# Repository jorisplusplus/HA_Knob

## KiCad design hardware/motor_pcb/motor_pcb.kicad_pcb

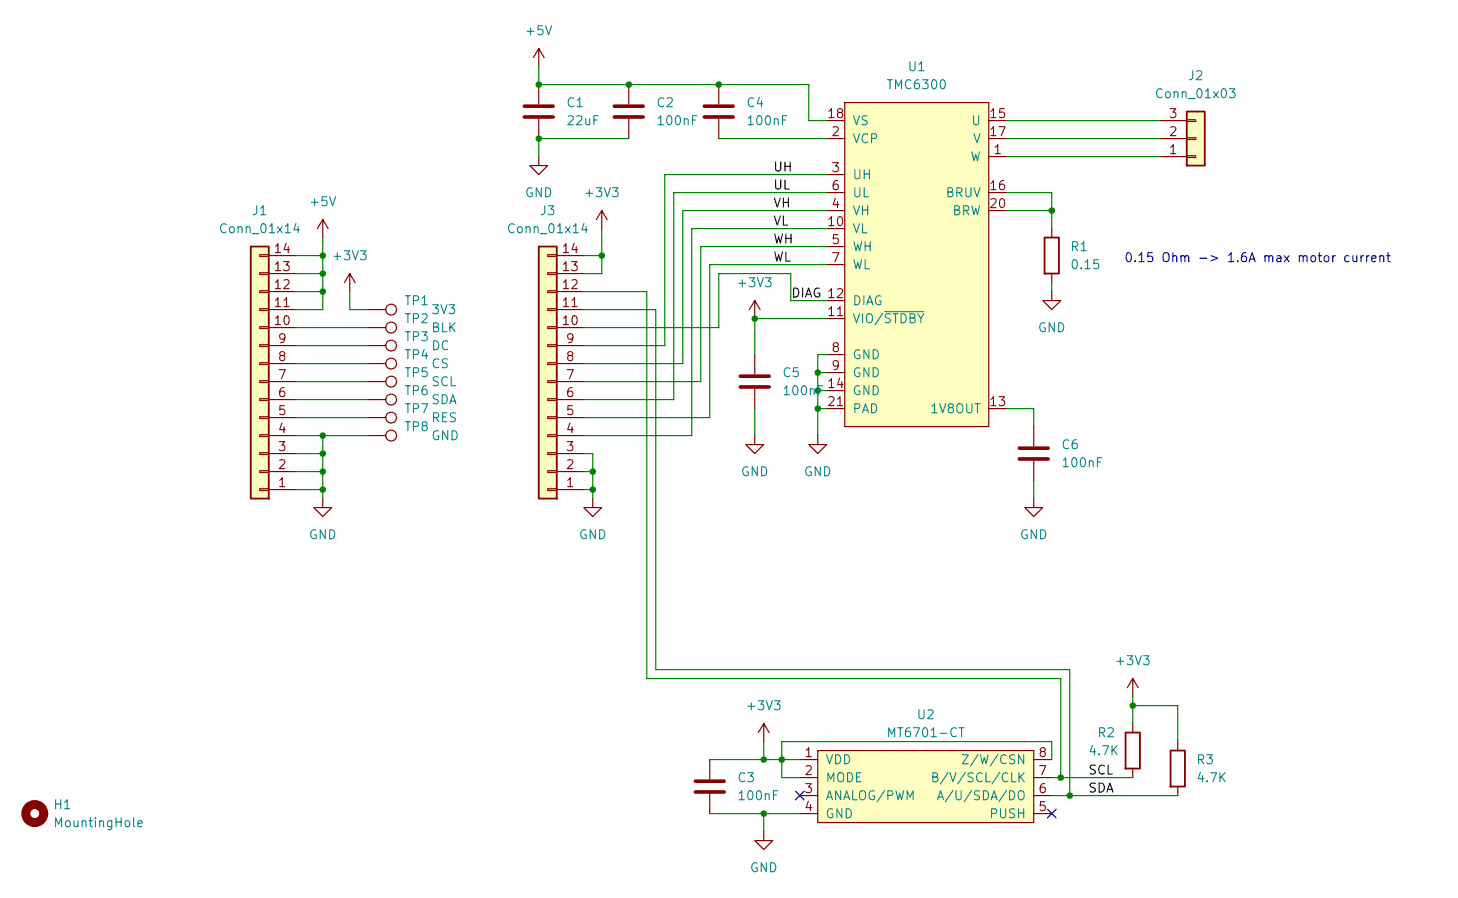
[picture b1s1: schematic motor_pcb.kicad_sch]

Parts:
C1: 22uF; C_0805_2012Metric; LCSC C45783
C2, C3, C4, C5, C6: 100nF; C_0603_1608Metric; LCSC C14663
H1: MountingHole; Holes
J1, J3: Conn_01x14; FPC_14; LCSC C262561
J2: Conn_01x03; Hirose_DF52-3S-0.8H_1x03-1MP_P0.80mm_Horizontal; LCSC C500138
R1: 0.15; R_1206_3216Metric; LCSC C37936
R2, R3: 4.7K; R_0603_1608Metric; LCSC C23162
TP1: 3V3; TestPoint_Pad_2.0x2.0mm
TP2: BLK; TestPoint_Pad_2.0x2.0mm
TP3: DC; TestPoint_Pad_2.0x2.0mm
TP4: CS; TestPoint_Pad_2.0x2.0mm
TP5: SCL; TestPoint_Pad_2.0x2.0mm
TP6: SDA; TestPoint_Pad_2.0x2.0mm
TP7: RES; TestPoint_Pad_2.0x2.0mm
TP8: GND; TestPoint_Pad_2.0x2.0mm
U1: TMC6300; QFN-20-1EP_3x3mm_P0.4mm_EP1.65x1.65mm_ThermalVias
U2: MT6701-CT; SOIC-8_3.9x4.9mm_P1.27mm; LCSC C2856764

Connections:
+3V3: C3.1, C5.1, J3.13, J3.14, R2.1, R3.1, TP1.1, U1.11 (VIO/~STDBY), U2.1 (VDD), U2.2 (MODE), U2.8 (Z/W/CSN)
+5V: C1.1, C2.1, C4.1, J1.11, J1.12, J1.13, J1.14, U1.18 (VS)
/DIAG: J3.10, U1.12 (DIAG)
/SCL: J3.12, R2.2, U2.7 (B/V/SCL/CLK)
/SDA: J3.11, R3.2, U2.6 (A/U/SDA/DO)
/UH: J3.9, U1.3 (UH)
/UL: J3.6, U1.6 (UL)
/VH: J3.8, U1.4 (VH)
/VL: J3.4, U1.10 (VL)
/WH: J3.7, U1.5 (WH)
/WL: J3.5, U1.7 (WL)
GND: C1.2, C2.2, C3.2, C5.2, C6.2, J1.1, J1.2, J1.3, J1.4, J3.1, J3.2, J3.3, R1.2, TP8.1, U1.8 (GND), U1.9 (GND), U1.14 (GND), U1.21 (PAD), U2.4 (GND)
unnamed: C4.2, U1.2 (VCP)
unnamed: C6.1, U1.13 (1V8OUT)
unnamed: J1.5, TP7.1
unnamed: J1.6, TP6.1
unnamed: J1.7, TP5.1
unnamed: J1.8, TP4.1
unnamed: J1.9, TP3.1
unnamed: J1.10, TP2.1
unnamed: J2.1, U1.1 (W)
unnamed: J2.2, U1.17 (V)
unnamed: J2.3, U1.15 (U)
unnamed: R1.1, U1.16 (BRUV), U1.20 (BRW)

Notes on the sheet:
0.15 Ohm -> 1.6A max motor current

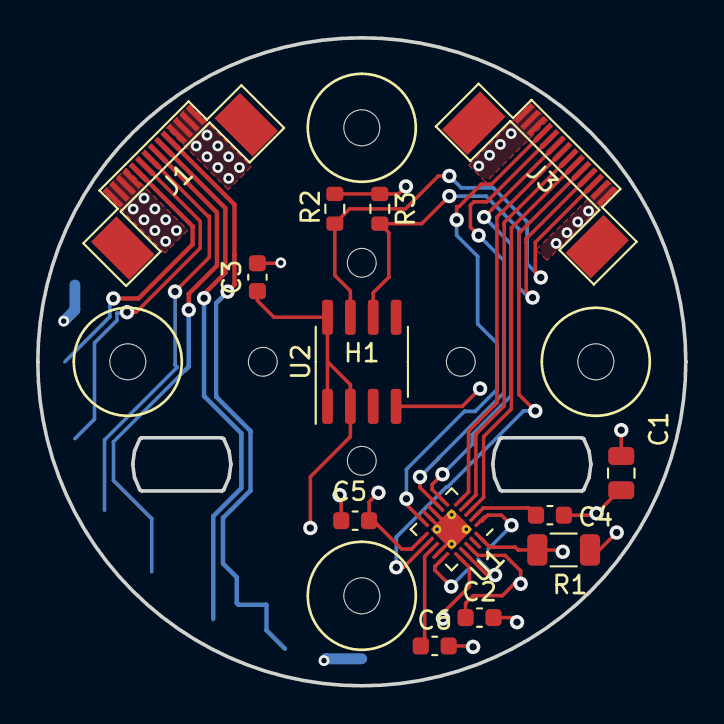
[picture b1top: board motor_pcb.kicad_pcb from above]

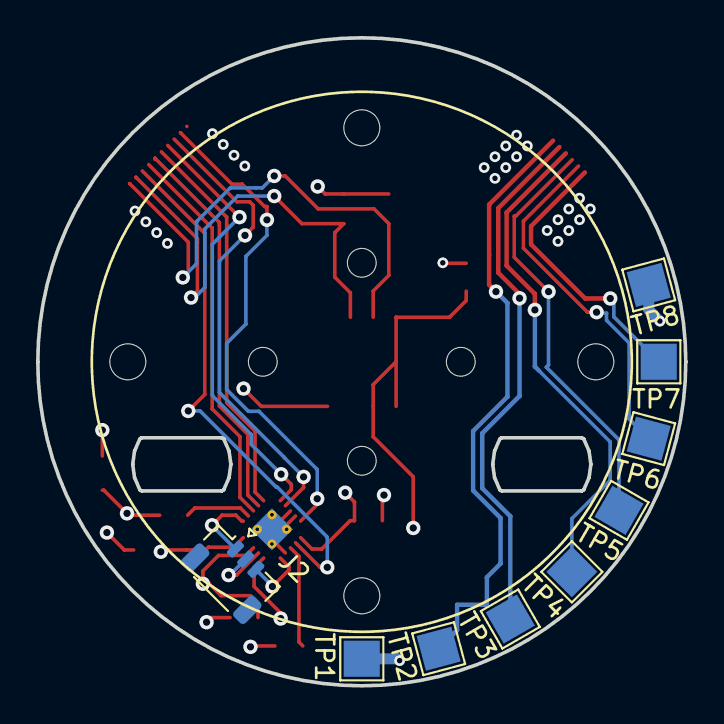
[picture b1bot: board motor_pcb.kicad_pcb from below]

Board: 4 copper layers, 36.0 x 36.0 mm, 23 parts (9 on the bottom side), 24 nets.

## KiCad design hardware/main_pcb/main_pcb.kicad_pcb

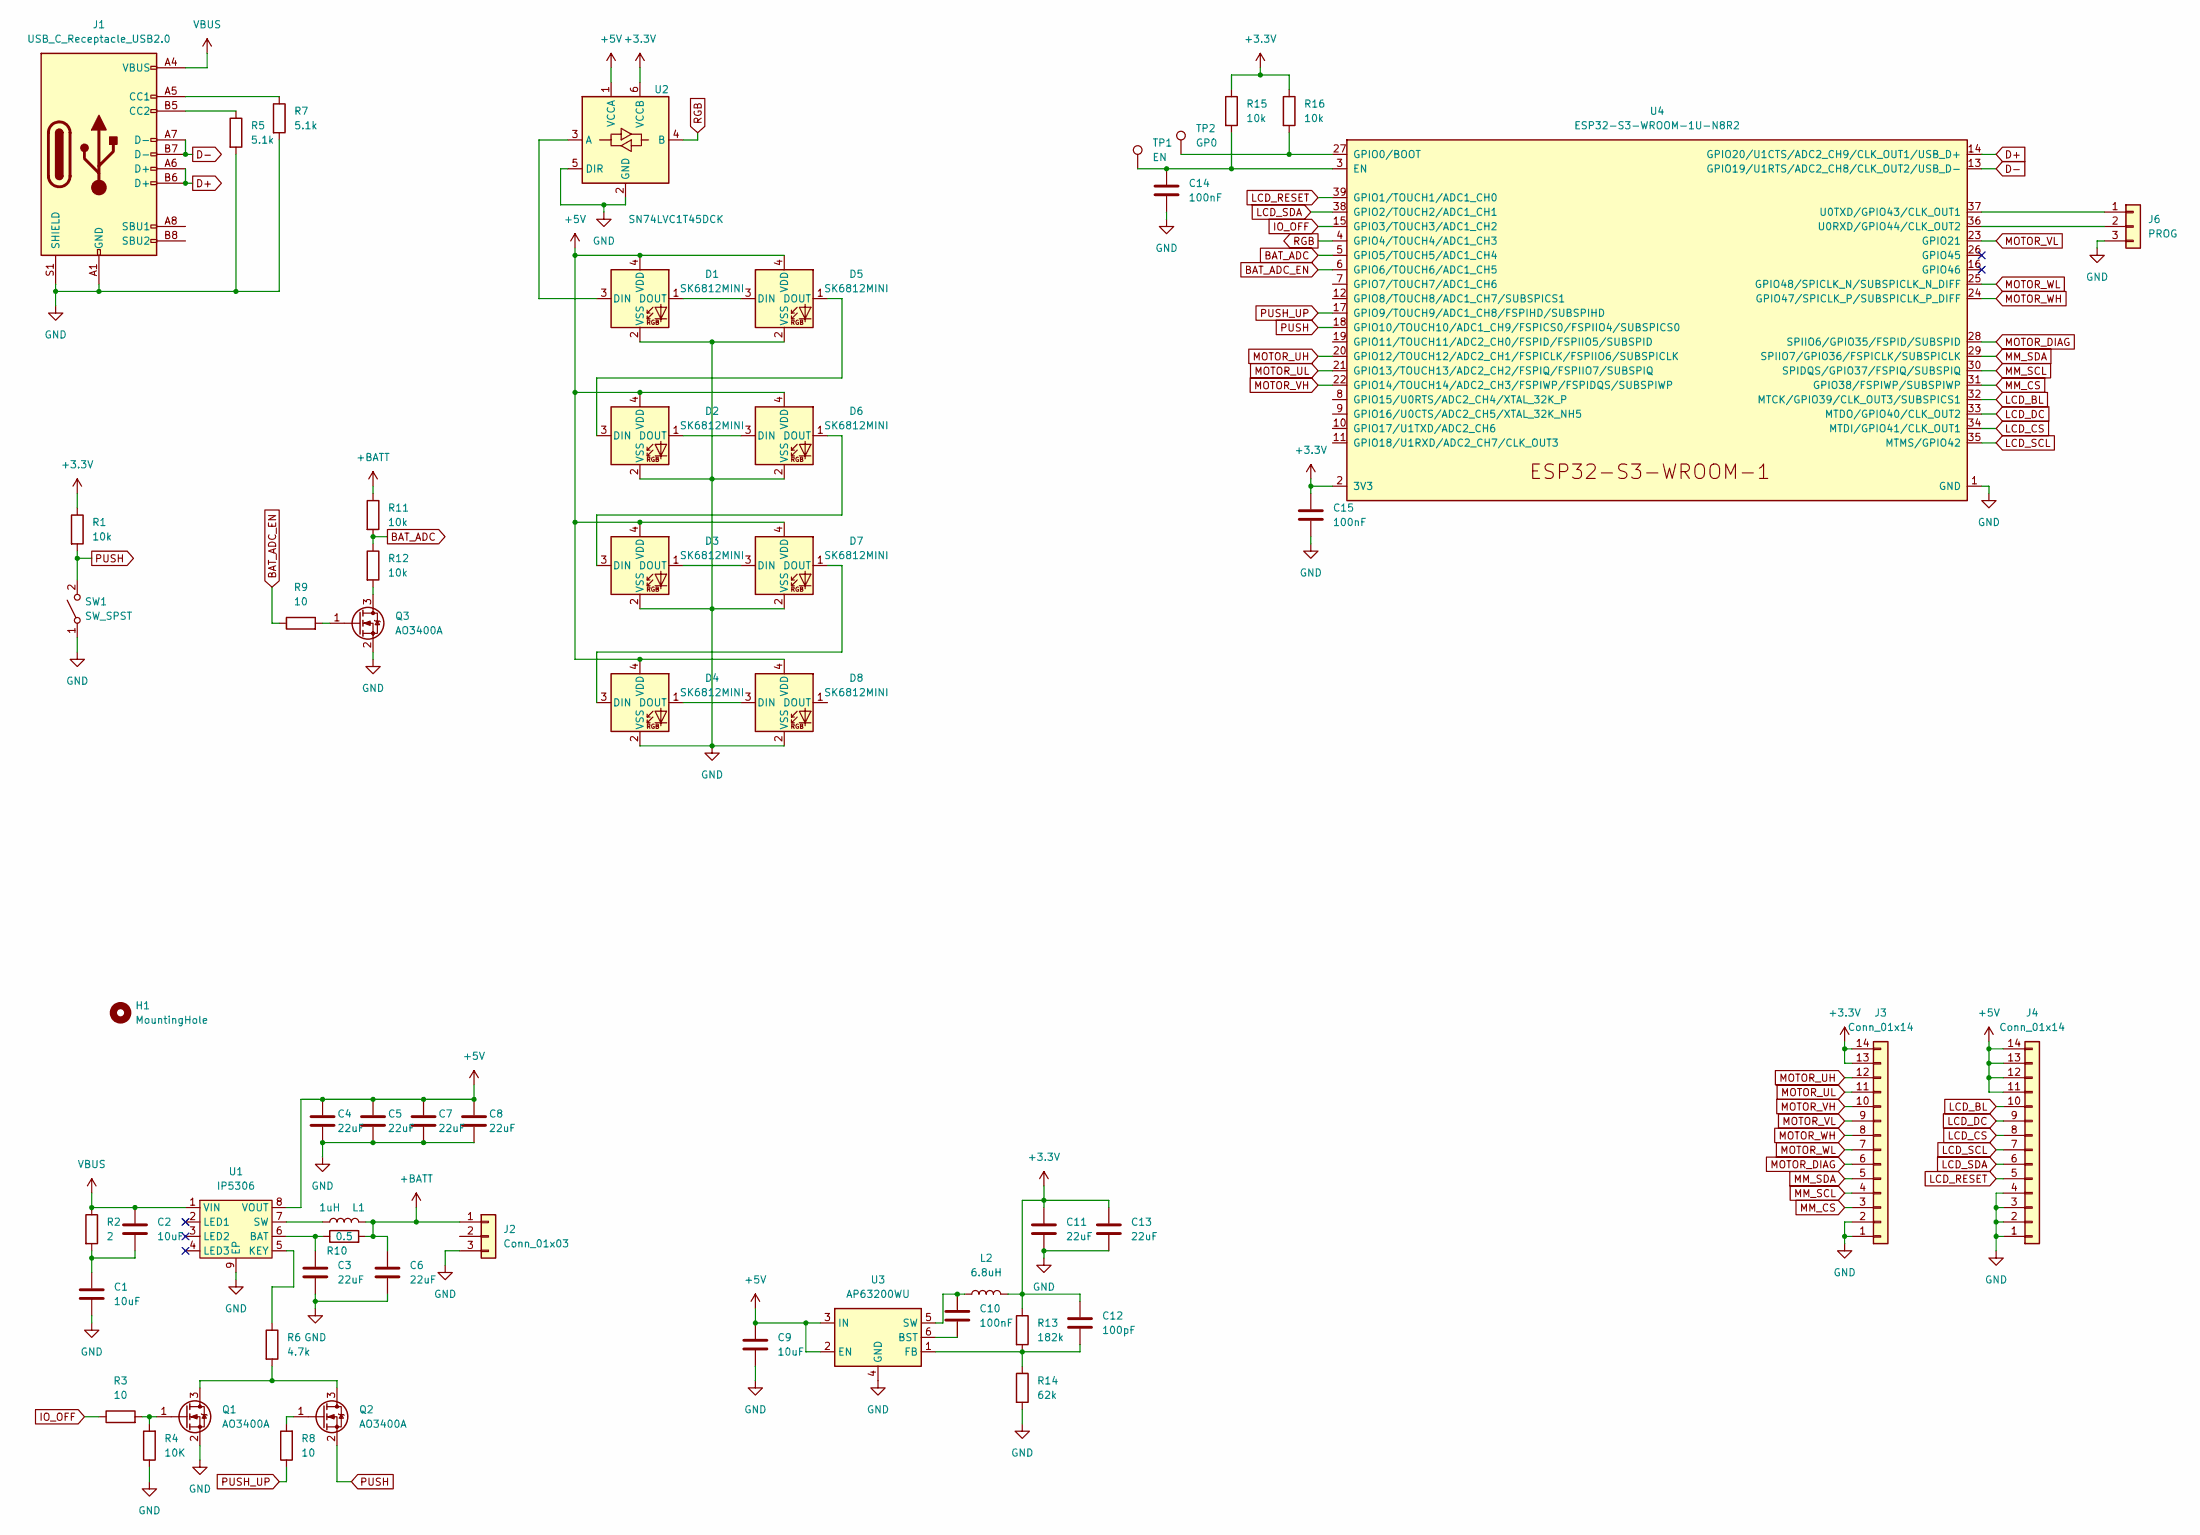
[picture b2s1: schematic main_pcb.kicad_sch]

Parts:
C1, C2, C9: 10uF; C_0603_1608Metric
C3, C4, C5, C6, C7, C8, C11, C13: 22uF; C_0805_2012Metric
C10, C14, C15: 100nF; C_0603_1608Metric
C12: 100pF; C_0603_1608Metric
D1, D2, D3, D4, D5, D6, D7, D8: SK6812MINI; LED_SK6812MINI_PLCC4_3.5x3.5mm_P1.75mm
H1: MountingHole; holes
J1: USB_C_Receptacle_USB2.0; USB_C_Receptacle_HRO_TYPE-C-31-M-12; LCSC C165948
J2: Conn_01x03; Molex_PicoBlade_53261-0371_1x03-1MP_P1.25mm_Horizontal
J3, J4: Conn_01x14; FPC_14; LCSC C262561
J6: PROG; PinHeader_1x03_P2.54mm_Vertical
L1: 1uH; MWSA0402S-6R8MT; LCSC C408332
L2: 6.8uH; MWSA0402S-6R8MT; LCSC C408338
Q1, Q2, Q3: AO3400A; SOT-23
R1, R11, R12, R15, R16: 10k; R_0603_1608Metric
R2: 2; R_0603_1608Metric
R3, R8, R9: 10; R_0603_1608Metric
R4: 10K; R_0603_1608Metric
R5, R7: 5.1k; R_0603_1608Metric
R6: 4.7k; R_0603_1608Metric
R10: 0.5; R_0603_1608Metric
R13: 182k; R_0603_1608Metric
R14: 62k; R_0603_1608Metric
SW1: SW_SPST; TS-1068A-A2B3-D2; LCSC C498297
TP1: EN; TestPoint_Pad_D2.0mm
TP2: GP0; TestPoint_Pad_D2.0mm
U1: IP5306; SOP-8-1EP_4.57x4.57mm_P1.27mm_EP4.57x4.45mm_ThermalVias
U2: SN74LVC1T45DCK; SOT-363_SC-70-6
U3: AP63200WU; TSOT-23-6
U4: ESP32-S3-WROOM-1U-N8R2; ESP32-S3-WROOM-1U

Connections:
+3.3V: C11.1, C12.1, C13.1, C15.1, J3.13, J3.14, L2.2, R1.1, R13.1, R15.1, R16.1, U2.6 (VCCB), U4.2 (3V3)
+5V: C4.1, C5.1, C7.1, C8.1, C9.1, D1.4 (VDD), D2.4 (VDD), D3.4 (VDD), D4.4 (VDD), D5.4 (VDD), D6.4 (VDD), D7.4 (VDD), D8.4 (VDD), J4.11, J4.12, J4.13, J4.14, U1.8 (VOUT), U2.1 (VCCA), U3.2 (EN), U3.3 (IN)
+BATT: C6.1, J2.1, L1.2, R10.2, R11.1
BAT_ADC: R11.2, R12.1, U4.5 (GPIO5/TOUCH5/ADC1_CH4)
BAT_ADC_EN: R9.1, U4.6 (GPIO6/TOUCH6/ADC1_CH5)
D+: J1.A6 (D+), J1.B6 (D+), U4.14 (GPIO20/U1CTS/ADC2_CH9/CLK_OUT1/USB_D+)
D-: J1.A7 (D-), J1.B7 (D-), U4.13 (GPIO19/U1RTS/ADC2_CH8/CLK_OUT2/USB_D-)
GND: C1.2, C3.2, C4.2, C5.2, C6.2, C7.2, C8.2, C9.2, C11.2, C13.2, C14.2, C15.2, D1.2 (VSS), D2.2 (VSS), D3.2 (VSS), D4.2 (VSS), D5.2 (VSS), D6.2 (VSS), D7.2 (VSS), D8.2 (VSS), J1.A1 (GND), J1.A12 (GND), J1.B1 (GND), J1.B12 (GND), J1.S1 (SHIELD), J2.3, J3.1, J3.2, J4.1, J4.2, J4.3, J4.4, J6.3, Q1.2 (S), Q3.2 (S), R4.1, R5.2, R7.2, R14.2, SW1.1 (A), U1.9 (EP), U2.2 (GND), U2.5 (DIR), U3.4 (GND), U4.1 (GND), U4.40 (GND), U4.41 (GND)
IO_OFF: R3.1, U4.15 (GPIO3/TOUCH3/ADC1_CH2)
LCD_BL: J4.10, U4.32 (MTCK/GPIO39/CLK_OUT3/SUBSPICS1)
LCD_CS: J4.8, U4.34 (MTDI/GPIO41/CLK_OUT1)
LCD_DC: J4.9, U4.33 (MTDO/GPIO40/CLK_OUT2)
LCD_RESET: J4.5, U4.39 (GPIO1/TOUCH1/ADC1_CH0)
LCD_SCL: J4.7, U4.35 (MTMS/GPIO42)
LCD_SDA: J4.6, U4.38 (GPIO2/TOUCH2/ADC1_CH1)
MM_CS: J3.3, U4.31 (GPIO38/FSPIWP/SUBSPIWP)
MM_SCL: J3.4, U4.30 (SPIDQS/GPIO37/FSPIQ/SUBSPIQ)
MM_SDA: J3.5, U4.29 (SPIIO7/GPIO36/FSPICLK/SUBSPICLK)
MOTOR_DIAG: J3.6, U4.28 (SPIIO6/GPIO35/FSPID/SUBSPID)
MOTOR_UH: J3.12, U4.20 (GPIO12/TOUCH12/ADC2_CH1/FSPICLK/FSPIIO6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)
MOTOR_UL: J3.11, U4.21 (GPIO13/TOUCH13/ADC2_CH2/FSPIQ/FSPIIO7/S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)
MOTOR_VH: J3.10, U4.22 (GPIO14/TOUCH14/ADC2_CH3/FSPIWP/FSPIDQS/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)
MOTOR_VL: J3.9, U4.23 (GPIO21)
MOTOR_WH: J3.8, U4.24 (GPIO47/SPICLK_P/SUBSPICLK_P_DIFF)
MOTOR_WL: J3.7, U4.25 (GPIO48/SPICLK_N/SUBSPICLK_N_DIFF)
unnamed: C1.1, C2.2, R2.2
unnamed: C3.1, R10.1, U1.6 (BAT)
unnamed: C10.1, L2.1, U3.5 (SW)
unnamed: C10.2, U3.6 (BST)
unnamed: C12.2, R13.2, R14.1, U3.1 (FB)
unnamed: C14.1, R15.2, TP1.1, U4.3 (EN)
unnamed: D1.1 (DOUT), D5.3 (DIN)
unnamed: D1.3 (DIN), U2.3 (A)
unnamed: D2.1 (DOUT), D6.3 (DIN)
unnamed: D2.3 (DIN), D5.1 (DOUT)
unnamed: D3.1 (DOUT), D7.3 (DIN)
unnamed: D3.3 (DIN), D6.1 (DOUT)
unnamed: D4.1 (DOUT), D8.3 (DIN)
unnamed: D4.3 (DIN), D7.1 (DOUT)
unnamed: J1.A5 (CC1), R7.1
unnamed: J1.B5 (CC2), R5.1
unnamed: J6.1, U4.37 (U0TXD/GPIO43/CLK_OUT1)
unnamed: J6.2, U4.36 (U0RXD/GPIO44/CLK_OUT2)
unnamed: L1.1, U1.7 (SW)
unnamed: Q1.1 (G), R3.2, R4.2
unnamed: Q1.3 (D), Q2.3 (D), R6.2
unnamed: Q2.1 (G), R8.2
unnamed: Q3.1 (G), R9.2
unnamed: Q3.3 (D), R12.2
unnamed: R6.1, U1.5 (KEY)
unnamed: R16.2, TP2.1, U4.27 (GPIO0/BOOT)
PUSH: Q2.2 (S), R1.2, SW1.2 (B), U4.18 (GPIO10/TOUCH10/ADC1_CH9/FSPICS0/FSPIIO4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)
PUSH_UP: R8.1, U4.17 (GPIO9/TOUCH9/ADC1_CH8/FSPIHD/SUBSPIHD)
RGB: U2.4 (B), U4.4 (GPIO4/TOUCH4/ADC1_CH3)
VBUS: C2.1, J1.A4 (VBUS), J1.A9 (VBUS), J1.B4 (VBUS), J1.B9 (VBUS), R2.1, U1.1 (VIN)

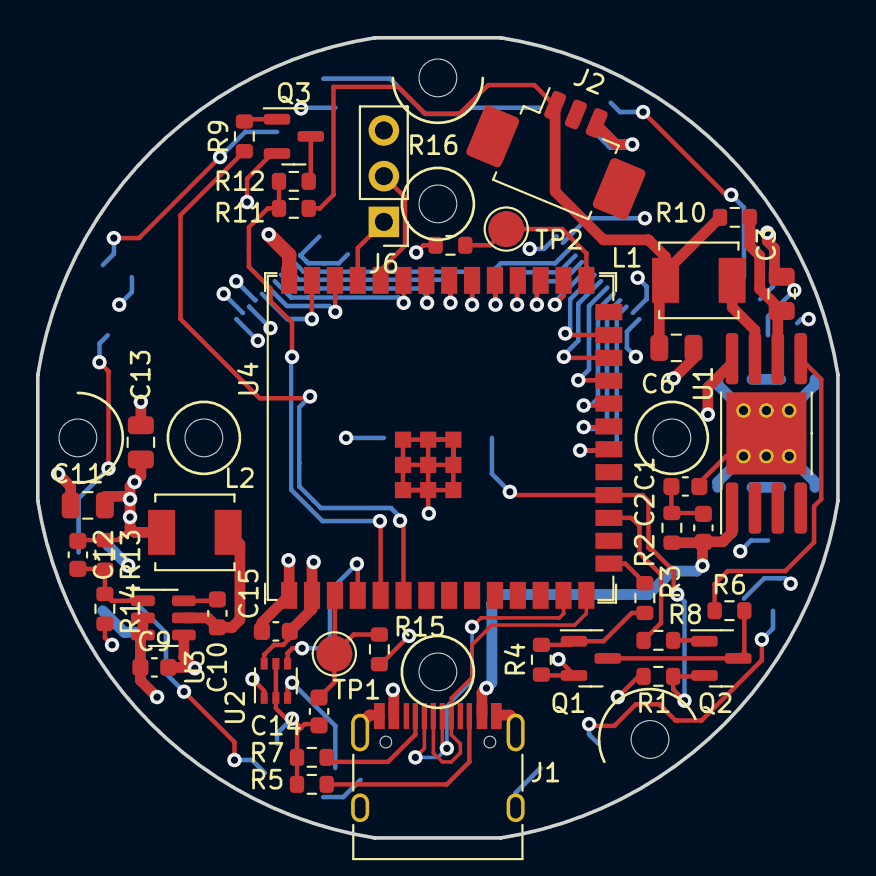
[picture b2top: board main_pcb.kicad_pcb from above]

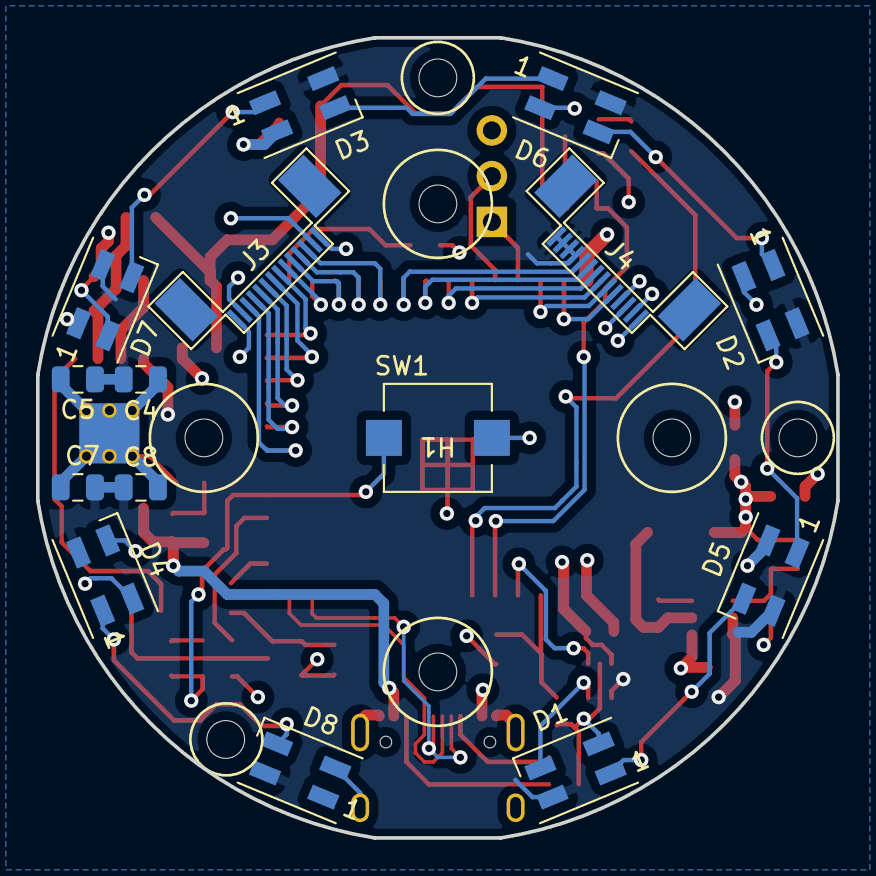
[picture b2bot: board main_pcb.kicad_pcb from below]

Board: 4 copper layers, 44.5 x 44.5 mm, 57 parts (16 on the bottom side), 55 nets.

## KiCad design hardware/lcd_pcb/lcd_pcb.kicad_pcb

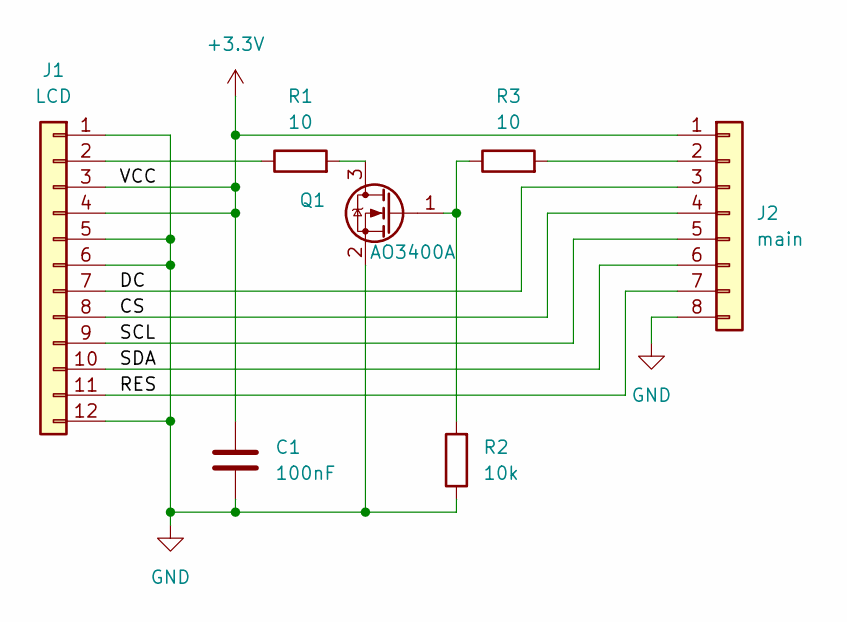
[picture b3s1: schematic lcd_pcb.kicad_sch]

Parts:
C1: 100nF; C_0603_1608Metric
J1: LCD; GC9A01Round1.28
J2: main; Hirose_DF52-8S-0.8H_1x08-1MP_P0.80mm_Horizontal
Q1: AO3400A; SOT-23
R1, R3: 10; R_0603_1608Metric
R2: 10k; R_0603_1608Metric

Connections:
+3.3V: C1.1, J1.3, J1.4, J2.1
/CS: J1.8, J2.4
/DC: J1.7, J2.3
/RES: J1.11, J2.7
/SCL: J1.9, J2.5
/SDA: J1.10, J2.6
GND: C1.2, J1.1, J1.5, J1.6, J1.12, J2.8, Q1.2 (S), R2.1
unnamed: J1.2, R1.1
unnamed: J2.2, R3.2
unnamed: Q1.1 (G), R2.2, R3.1
unnamed: Q1.3 (D), R1.2

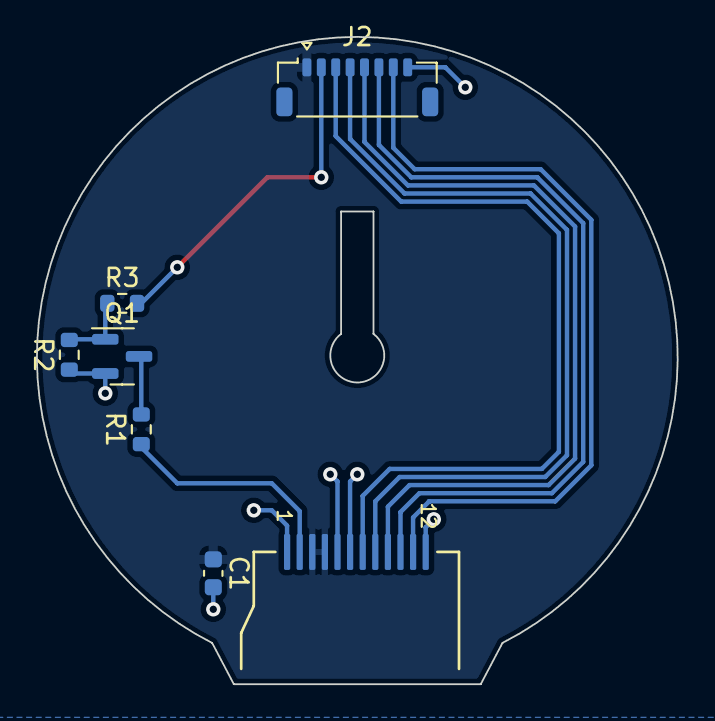
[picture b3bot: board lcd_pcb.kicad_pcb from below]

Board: 2 copper layers, 35.6 x 36.0 mm, 7 parts (7 on the bottom side), 11 nets.

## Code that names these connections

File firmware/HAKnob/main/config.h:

#pragma once

#include <driver/gpio.h>


//OLD
// #define GPIO_LCD_RESET  GPIO_NUM_1
// #define GPIO_LCD_SDA    GPIO_NUM_2
// #define GPIO_IO_OFF     GPIO_NUM_3
// #define GPIO_RGB        GPIO_NUM_4
// #define GPIO_BAT_ADC    GPIO_NUM_5
// #define GPIO_BAT_ADC_EN GPIO_NUM_6
// #define GPIO_PUSH_UP    GPIO_NUM_9
// #define GPIO_PUSH       GPIO_NUM_10
// #define GPIO_MOTOR_UH   GPIO_NUM_12
// #define GPIO_MOTOR_UL   GPIO_NUM_13
// #define GPIO_MOTOR_VH   GPIO_NUM_14
// #define GPIO_MOTOR_VL   GPIO_NUM_21
// #define GPIO_MOTOR_WL   GPIO_NUM_48
// #define GPIO_MOTOR_WH   GPIO_NUM_47
// #define GPIO_MOTOR_DIAG GPIO_NUM_35
// #define GPIO_MM_SDA     GPIO_NUM_36
// #define GPIO_MM_SCL     GPIO_NUM_37
// #define GPIO_MM_CS      GPIO_NUM_38
// #define GPIO_LCD_BL     GPIO_NUM_39
// #define GPIO_LCD_DC     GPIO_NUM_40
// #define GPIO_LCD_CS     GPIO_NUM_41
// #define GPIO_LCD_SCL    GPIO_NUM_42

//NEW
#define GPIO_IO_OFF     GPIO_NUM_3
#define GPIO_RGB        GPIO_NUM_4
#define GPIO_BAT_ADC    GPIO_NUM_5
#define GPIO_BAT_ADC_EN GPIO_NUM_6
#define GPIO_PUSH_UP    GPIO_NUM_9
#define GPIO_PUSH       GPIO_NUM_10
#define GPIO_MOTOR_UH   GPIO_NUM_21
#define GPIO_MOTOR_UL   GPIO_NUM_35
#define GPIO_MOTOR_VH   GPIO_NUM_47
#define GPIO_MOTOR_VL   GPIO_NUM_37
#define GPIO_MOTOR_WL   GPIO_NUM_36
#define GPIO_MOTOR_WH   GPIO_NUM_48
#define GPIO_MOTOR_DIAG GPIO_NUM_14
#define GPIO_MM_SDA     GPIO_NUM_13
#define GPIO_MM_SCL     GPIO_NUM_12
#define GPIO_MM_CS      -1
#define GPIO_LCD_BL     GPIO_NUM_39
#define GPIO_LCD_DC     GPIO_NUM_40
#define GPIO_LCD_CS     GPIO_NUM_41
#define GPIO_LCD_SCL    GPIO_NUM_42 
#define GPIO_LCD_RESET  GPIO_NUM_1
#define GPIO_LCD_SDA    GPIO_NUM_2

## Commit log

2022-12-10 Added readme
2022-12-10 Added hardware folder
2022-12-10 Added schematic
2022-12-10 Initial motor schematic
2022-12-10 Added libs
2022-12-10 Updated schematic
2022-12-10 Updated power connector
2022-12-10 Added footprint for lcd
2022-12-10 Updated main pcb design
2022-12-11 Added component footprints
2022-12-11 Switch to 4 layer pcb
2022-12-11 Changed to fpc connector
2022-12-11 Updated lcsc number
2022-12-12 Added bom
2022-12-12 BOM update
2022-12-13 Updated bom
2022-12-13 Updated design with new wiring structure
2022-12-13 Updated connectors
2022-12-16 Added footprint lcd
2022-12-19 Updated bom with new fpc
2022-12-19 Updated battery connector
2022-12-20 Routed motor pcb
2022-12-20 Fixed stackup
2022-12-20 Finished routing
2022-12-23 Fixed drc errors
2022-12-23 Added gerbers generates
2022-12-23 Call script with bash
2022-12-23 Install kicad
2022-12-23 Use sudo
2022-12-25 Designed lcd pcb
2023-01-06 Initial route
2023-01-07 Switched to debian
2023-01-07 Changed to kicad ppa
2023-03-04 Fixed routing
2023-04-13 Updated modules
2023-04-13 Initial firmware
2023-04-13 Added ignore
2023-04-16 Refactored motor driver
2023-04-17 Some form of FOC
2023-04-17 Added calculations for speed
2023-04-17 Added controller
2023-05-09 Updated motor driver
2023-05-09 Updated sdkconfig
2023-05-09 Increased control loop stability
2023-05-13 Changed PID and increased PWM
2023-05-29 Added indent functions
2023-05-29 Fixed indent support
2023-06-01 Various debugging changes
2023-06-01 Use spi
2023-06-01 Reduced spi speed
2023-06-01 Fixed wrap around averaging
2023-06-01 Float optimization
2023-06-02 Updated PID values
2023-06-02 Add indent power support
2023-06-02 Use task notify instead of continuous polling
2023-06-21 Fixed bug in indenting
